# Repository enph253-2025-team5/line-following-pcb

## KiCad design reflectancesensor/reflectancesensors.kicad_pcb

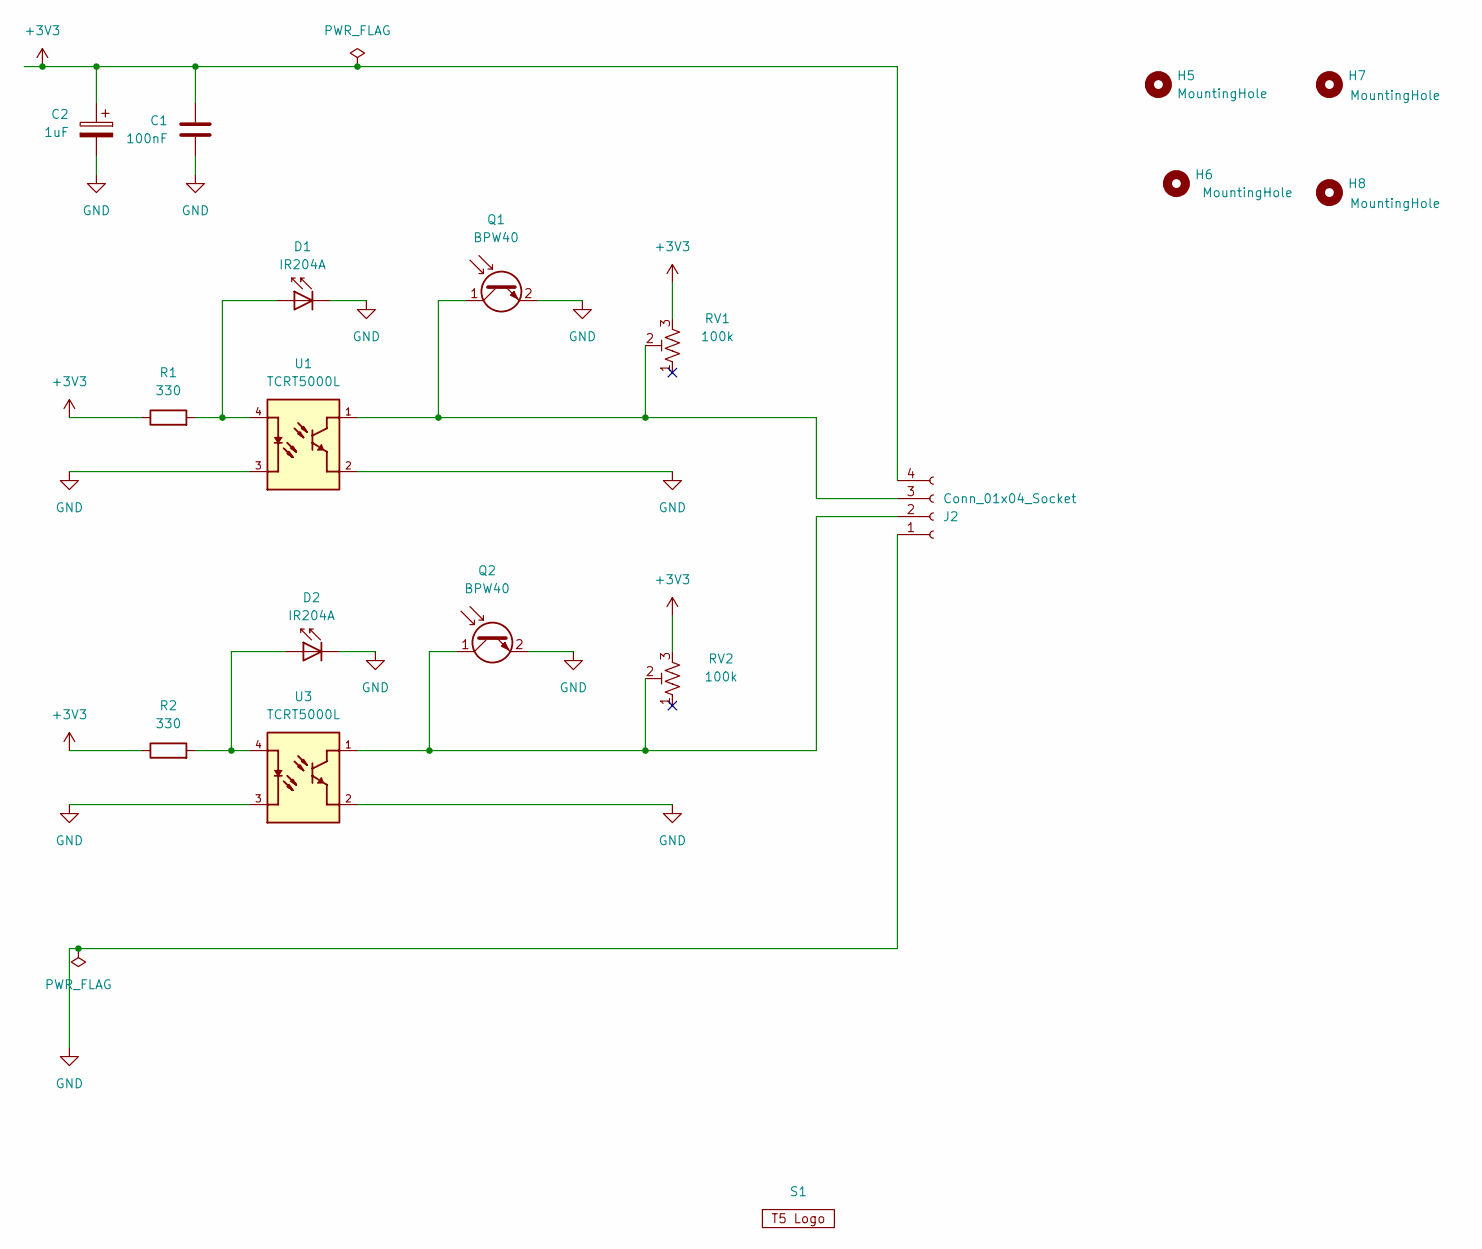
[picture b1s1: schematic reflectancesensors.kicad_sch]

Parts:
C1: 100nF; C_Disc_D3.0mm_W2.0mm_P2.50mm; Mfr. Part # TCC0402X5R104K160AT; LCSC ID C344189
C2: 1uF; CP_Radial_D5.0mm_P2.50mm
D1, D2: IR204A; LED_D5.0mm
H5, H6, H7, H8: MountingHole; MountingHole_3.2mm_M3_DIN965
J2: Conn_01x04_Socket; JST_XH_S4B-XH-A-1_1x04_P2.50mm_Horizontal
Q1, Q2: BPW40; LED_D5.0mm_Clear
R1, R2: 330; R_Axial_DIN0309_L9.0mm_D3.2mm_P12.70mm_Horizontal
RV1, RV2: 100k; Potentiometer_Bourns_3266Y_Vertical
S1: Logo; ENPH253_Logo
U1, U3: TCRT5000L; Vishay_TCRT5000

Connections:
+3V3: C1.1, C2.1, J2.4, R1.1, R2.1, RV1.3, RV2.3
GND: C1.2, C2.2, D1.1 (K), D2.1 (K), J2.1, Q1.2 (E), Q2.2 (E), U1.2, U1.3, U3.2, U3.3
unnamed: D1.2 (A), R1.2, U1.4
unnamed: D2.2 (A), R2.2, U3.4
unnamed: J2.2, Q2.1 (C), RV2.2, U3.1
unnamed: J2.3, Q1.1 (C), RV1.2, U1.1

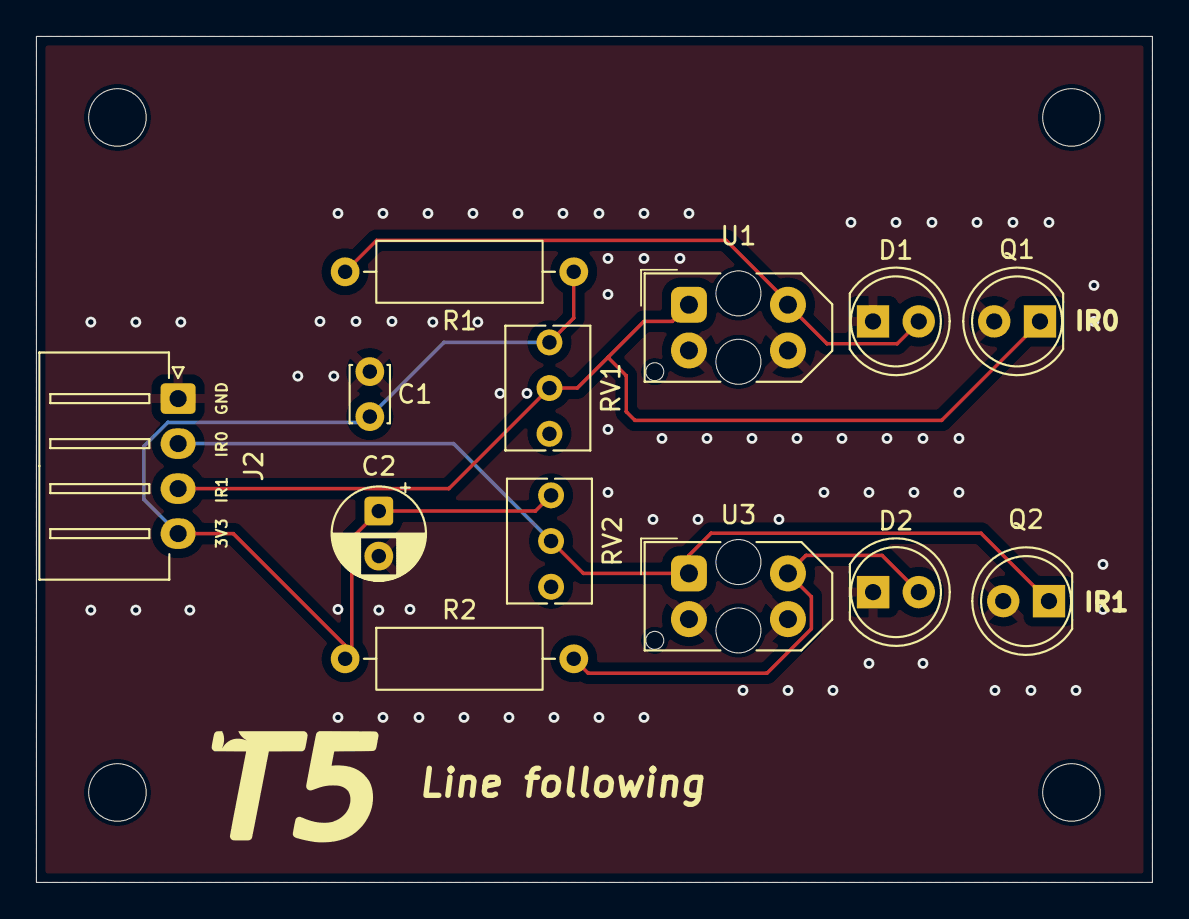
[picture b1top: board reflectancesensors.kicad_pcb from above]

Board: 2 copper layers, 62.0 x 47.0 mm, 18 parts (0 on the bottom side), 6 nets.

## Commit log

2025-06-20 add a gitignore
2025-06-20 adding all files
2025-06-22 some small changes
2025-06-26 adding high power reflectance
2025-06-27 small changes
2025-07-03 changing connector
2025-07-04 adding labels and editing traces
2025-07-04 final touches
2025-07-04 adding gerber files
2025-07-04 updated mounting holes
2025-07-04 fixing multiple versions
2025-07-04 Some fixes
